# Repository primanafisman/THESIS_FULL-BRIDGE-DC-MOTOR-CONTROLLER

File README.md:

# Hi there

These are prima's thesis.

I'm working at Fullbridge DC Motor Controller. Create model, hardware, and firmware to controll the steering DC Motor

Let's have a look!

Any further improvements are always widthly open

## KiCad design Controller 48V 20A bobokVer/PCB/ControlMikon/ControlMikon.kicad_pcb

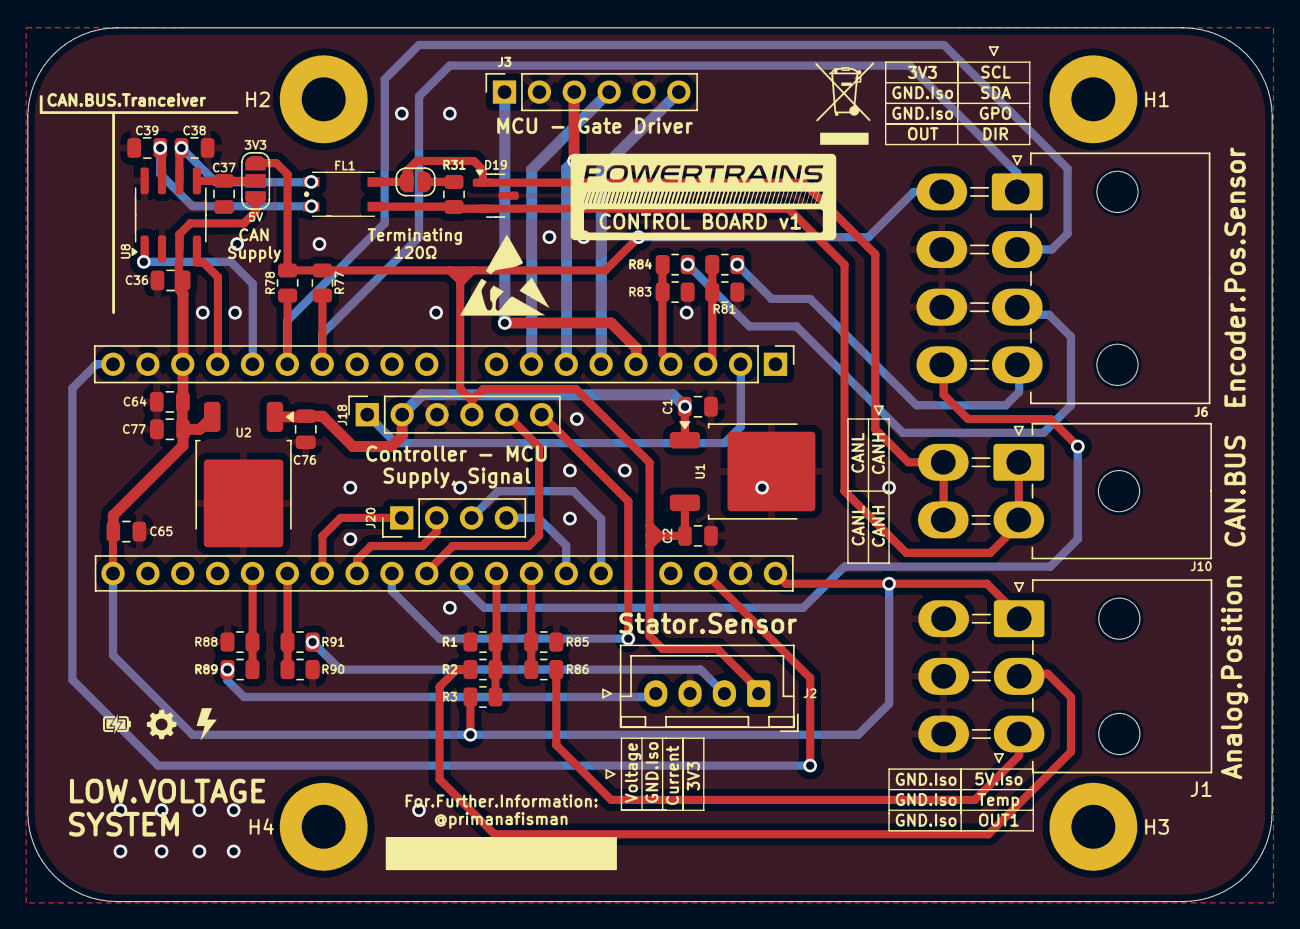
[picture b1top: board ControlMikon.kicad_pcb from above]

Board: 2 copper layers, 90.7 x 63.7 mm, 45 parts (0 on the bottom side), 39 nets.

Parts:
C1, C76: 330nF; C_0805_2012Metric
C2, C64, C65, C77: 100nF; C_0805_2012Metric
C36, C37: 1uF; C_0805_2012Metric
C38, C39: 220pf; C_0805_2012Metric
D19: PESD1CAN; SOT-23
FL1: DLW43MH201XK2K; DLW43
H1, H2, H3, H4: MountingHole; MountingHole_3.2mm_M3_Pad
J1: AnalogPosition; Molex_Mini-Fit_Jr_5569-06A2_2x03_P4.20mm_Horizontal
J2: From Current & Voltage Sense; JST_XH_B4B-XH-A_1x04_P2.50mm_Vertical
J3: Conn_01x06; PinSocket_1x06_P2.54mm_Vertical
J5: Selector Termination; SolderJumper-2_P1.3mm_Open_RoundedPad1.0x1.5mm
J6: Conn_01x08; Molex_Mini-Fit_Jr_5569-08A2_2x04_P4.20mm_Horizontal
J10: CANBUS; Molex_Mini-Fit_Jr_5569-04A2_2x02_P4.20mm_Horizontal
J18: Input Power; PinSocket_1x06_P2.54mm_Vertical
J20: AnalogPosition; PinHeader_1x04_P2.54mm_Vertical
JP5: Logic Level; SolderJumper-3_P1.3mm_Open_RoundedPad1.0x1.5mm_NumberLabels
R1, R2, R3, R77, R78, R81, R82, R83, R84, R85, R86: 1k; R_0805_2012Metric
R31: 120; R_0805_2012Metric
R88, R90: 3k3; R_0805_2012Metric
R89, R91: 1k8; R_0805_2012Metric
U1, U2: LM78M05_TO252; TO-252-2
U8: MCP2562-H-SN; SOIC-8_3.9x4.9mm_P1.27mm
U23: STM32F103CBTx; STM32F103CBT6

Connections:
3V3: C2.2, J2.1, J6.5, J18.4, JP5.3 (B), R77.1, R78.1, U1.3 (VO)
5VDigital_Isolated: C36.1, C64.1, C65.1, C77.2, J1.1, JP5.1 (A), R3.2, U2.3 (VO), U8.3 (VDD), U23.1 (VBAT), U23.24 (VDD), U23.36 (VDD)
12V_Isolated: C1.2, C76.2, J18.2, U1.1 (VI), U2.1 (VI)
/PRECHARGE_FINISH_TRIG: J18.1, U23.26 (PB13)
Aux1: J18.6, U23.14 (ADC1_IN4)
Aux2: J18.5, U23.15 (ADC1_IN5)
Aux3: R1.2, R2.1, R3.1, U23.17 (ADC1_IN7)
BATTV_Out: J20.1, U23.12 (ADC1_IN2)
CAL_L: C38.1, FL1.4, U8.6 (CANL)
CAN_H: C39.1, FL1.1, U8.7 (CANH)
CAN_H_Out: D19.2, FL1.2, J10.1, J10.2, R31.2
CAN_L_Out: D19.1, FL1.3, J5.1, J10.3, J10.4
CAN_Rx: U8.4 (RXD), U23.46 (CAN_TX)
CAN_Tx: U8.1 (TXD), U23.45 (CAN_RX)
CTRLV_Out: J20.2, U23.13 (ADC1_IN3)
CurrentSensor: R90.2, R91.1, U23.11 (ADC1_IN1)
DIR: R81.2, R82.1, U23.27 (PB14)
FinishLV: J20.4, U23.19 (PB1)
GND_Isolated: C1.1, C2.1, C36.2, C37.2, C38.2, C39.2, C64.2, C65.2, C76.1, C77.1, D19.3, J1.4, J1.5, J1.6, J2.3, J3.2, J3.5, J6.6, J6.7, J18.3, R1.1, R81.1, R83.1, R85.1, R88.1, R90.1, U1.2 (GND), U2.2 (GND), U8.2 (VSS), U8.8 (STBY), U23.8 (VSSA), U23.23 (VSS)
GPO: R83.2, R84.1, U23.28 (PB15)
HIN1_Mikon: J3.1, U23.29 (TIM1_CH1)
HIN2_Mikon: J3.3, U23.31 (TIM1_CH3)
LIN1_Mikon: J3.6, U23.30 (TIM1_CH2)
LIN2_Mikon: J3.4, U23.32 (TIM1_CH4)
unnamed: J1.2, R2.2
unnamed: J1.3, R86.2
unnamed: J2.2, R91.2
unnamed: J2.4, R89.2
unnamed: J5.2, R31.1
unnamed: J6.3, R84.2
unnamed: J6.4, R82.2
unnamed: C37.1, JP5.2 (C), U8.5 (Vio)
unnamed: U23.9 (VDDA), U23.48 (VDD)
Out: J6.8, U23.16 (ADC1_IN6)
Out1: R85.2, R86.1, U23.18 (ADC1_IN8)
Ready: J20.3, U23.20 (PB2)
SCL: J6.1, R77.2, U23.42 (I2C1_SCL)
SDA: J6.2, R78.2, U23.43 (I2C1_SDA)
VoltageSensor: R88.2, R89.1, U23.10 (ADC1_IN0)

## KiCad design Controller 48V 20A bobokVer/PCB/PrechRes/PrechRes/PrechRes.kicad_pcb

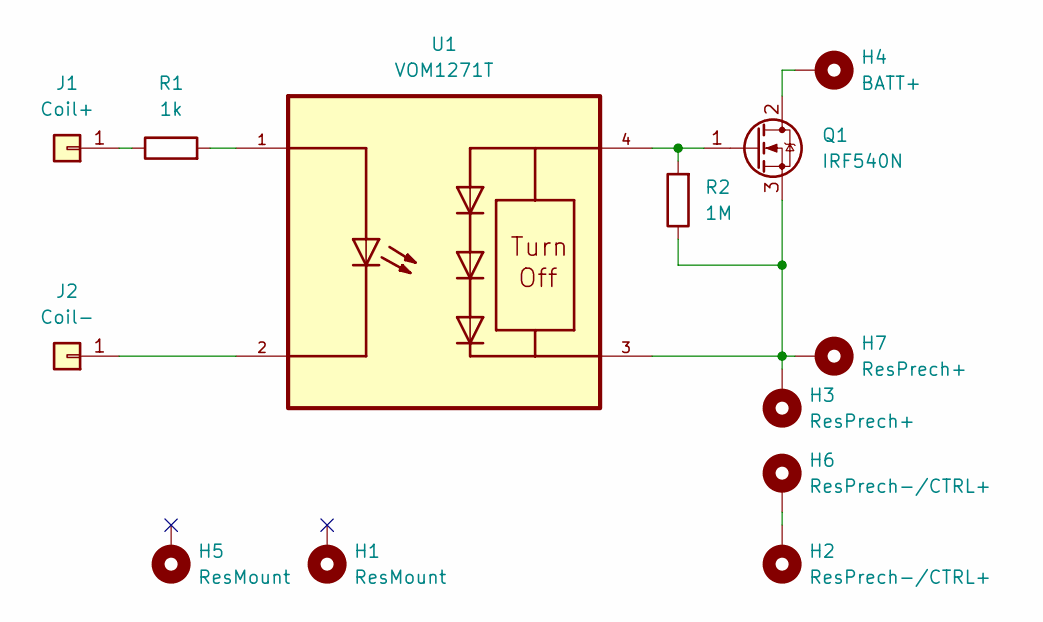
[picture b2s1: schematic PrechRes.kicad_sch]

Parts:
H1, H5: ResMount; MountingHole_3.2mm_M3
H2, H6: ResPrech-/CTRL+; MountingHole_3.2mm_M3_DIN965_Pad
H3, H7: ResPrech+; MountingHole_3.2mm_M3_DIN965_Pad
H4: BATT+; MountingHole_6.4mm_M6_DIN965_Pad
J1: Coil+; PinHeader_1x01_P2.54mm_Vertical
J2: Coil-; PinHeader_1x01_P2.54mm_Vertical
Q1: IRF540N; TO-220F-3_Horizontal_TabDown
R1: 1k; R_1206_3216Metric
R2: 1M; R_1206_3216Metric
U1: VOM1271T; SOIC254P695X242-4N

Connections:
unnamed: H2.1, H6.1
unnamed: J1.1, R1.1
unnamed: J2.1, U1.2
unnamed: H4.1, Q1.2 (D)
unnamed: Q1.1 (G), R2.2, U1.4
unnamed: H3.1, H7.1, Q1.3 (S), R2.1, U1.3
unnamed: R1.2, U1.1

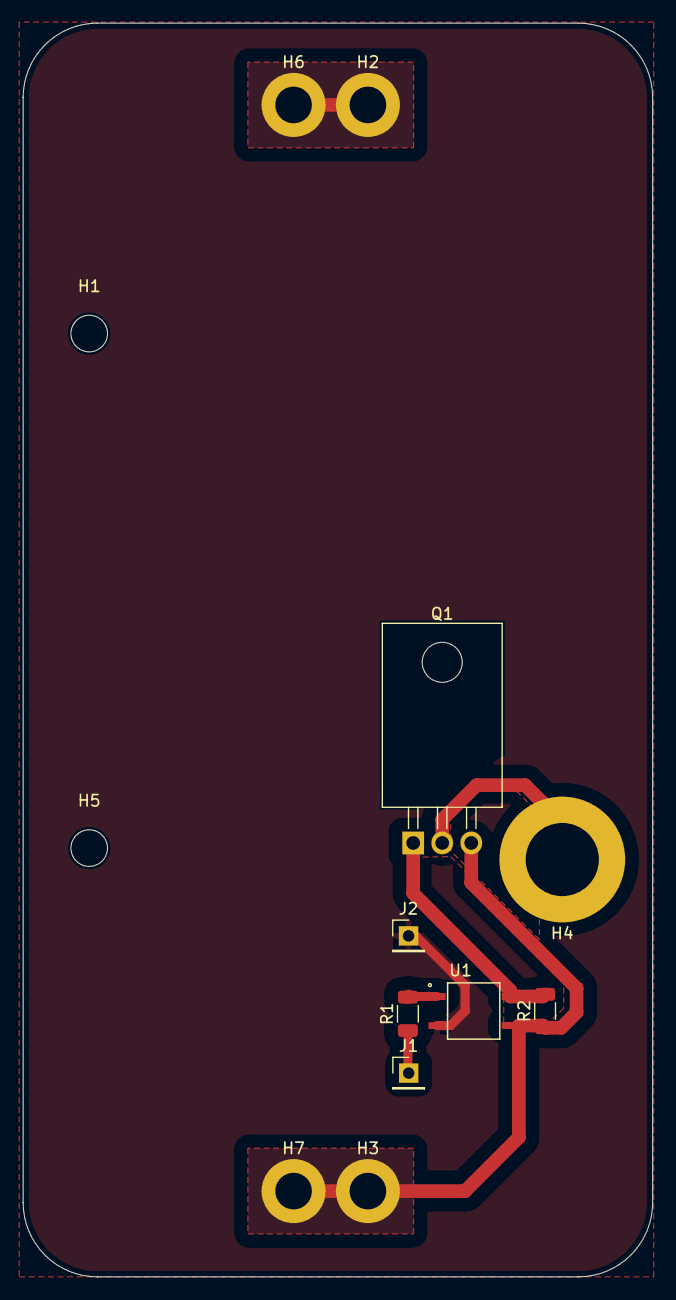
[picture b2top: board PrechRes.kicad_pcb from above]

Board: 2 copper layers, 55.1 x 109.7 mm, 13 parts (0 on the bottom side), 7 nets.

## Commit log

2026-02-03 Mengunggah file proyek pertama
